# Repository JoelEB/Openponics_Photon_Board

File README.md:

# Openponics_Photon_Board
A water testing platform based off the Particle Photon and the probes and stamps from Atlas Scientific.

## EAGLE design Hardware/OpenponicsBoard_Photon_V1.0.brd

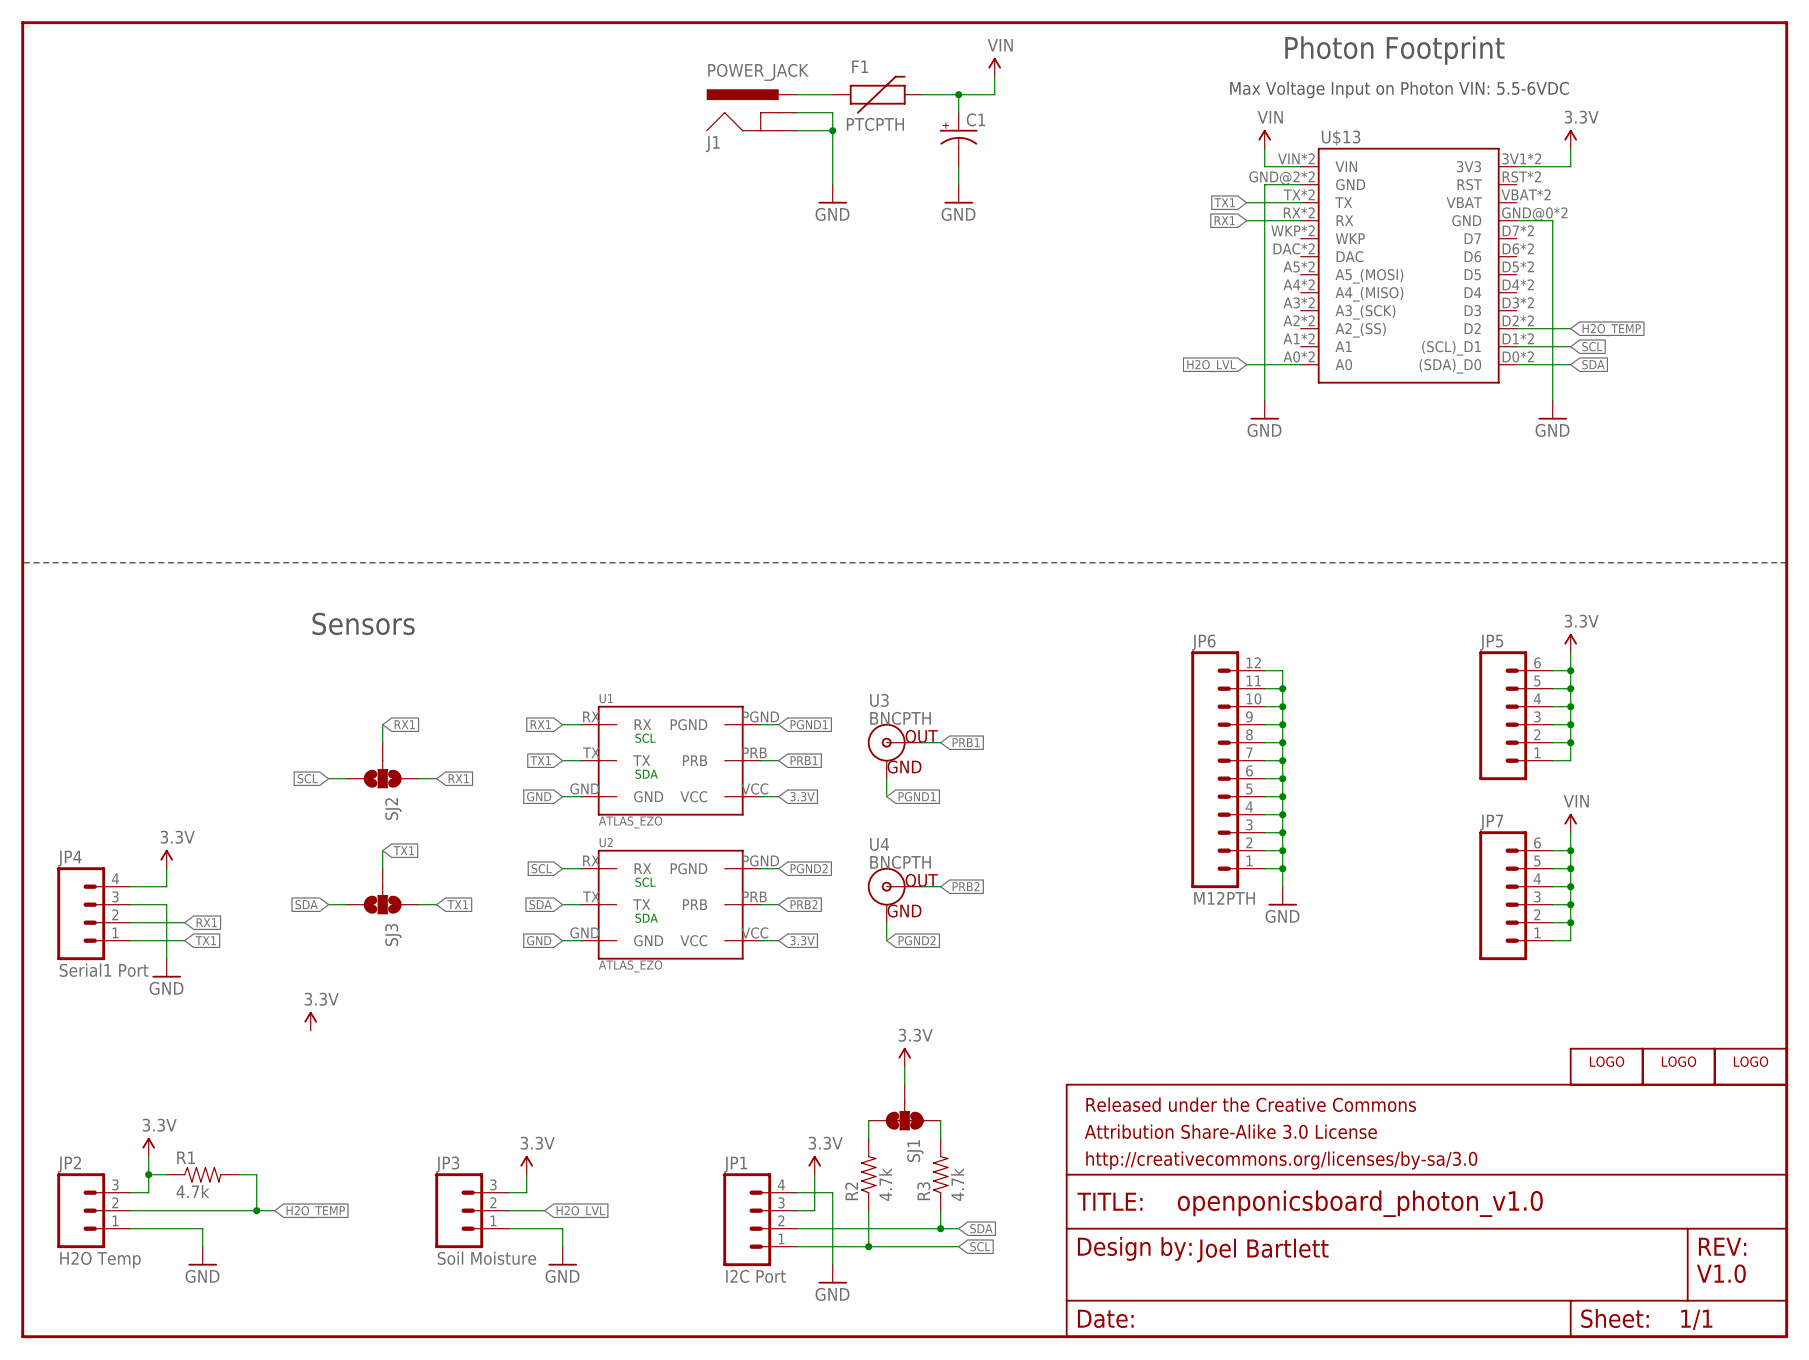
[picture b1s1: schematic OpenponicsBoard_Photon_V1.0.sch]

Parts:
C1: CAP_POLPTH1; CPOL-RADIAL-100UF-25V
F1: PTCPTH; PTC
FRAME1: FRAME-LETTER; CREATIVE_COMMONS
J1: POWER_JACK; POWER_JACK_PTH
JP1: I2C Port; 1X04
JP2: H2O Temp; 1X03
JP3: Soil Moisture; 1X03
JP4: Serial1 Port; 1X04
JP5, JP7: M06SIP; 1X06
JP6: M12PTH; 1X12
R1, R2, R3: 4.7k; AXIAL-0.4
SJ1: JUMPER-PAD-3-NC_BY_TRACE; PAD-JUMPER-3-3OF3_NC_BY_TRACE_YES_SILK_FULL_BOX
SJ2, SJ3: SOLDERJUMPER_2WAYS; SJ_3
U1, U2: ATLAS_EZO
U3, U4: BNCPTH; BNC
U$5: OPENPONICS_LOGO_SYMBOL
U$6: OPENPONICS_LOGO_SMALL
U$9: OPENPONICS_LOGO_SYMBOL_MED
U$13: PHOTON_FOOTPRINT_X2

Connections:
3.3V: JP1.3, JP2.3, JP3.3, JP4.4, JP5.1, JP5.2, JP5.3, JP5.4, JP5.5, JP5.6, R1.P$1 (1), SJ1.2, U1.VCC, U2.VCC, U$13.3V1 (3V3), U$13.3V3
GND: C1.2 (-), J1.GND, J1.GNDBREAK, JP1.4, JP2.1, JP3.1, JP4.3, JP6.1, JP6.2, JP6.3, JP6.4, JP6.5, JP6.6, JP6.7, JP6.8, JP6.9, JP6.10, JP6.11, JP6.12, U1.GND, U2.GND, U$13.GND@0 (GND), U$13.GND@1 (GND), U$13.GND@2 (GND), U$13.GND@2_1 (GND)
H2O_LVL: JP3.2, U$13.A0, U$13.A0_1 (A0)
H2O_TEMP: JP2.2, R1.P$2 (2), U$13.D2, U$13.D2_1 (D2)
unnamed: R2.P$2 (2), SJ1.3
unnamed: R3.P$2 (2), SJ1.1
PGND1: U1.PGND, U3.GND
PGND2: U2.PGND, U4.GND
PRB1: U1.PRB, U3.S (OUT)
PRB2: U2.PRB, U4.S (OUT)
RAW: F1.P$1 (1), J1.PWR
RX1: JP4.2, SJ2.1, SJ2.2, U1.RX, U$13.RX, U$13.RX1 (RX)
SCL: JP1.1, R2.P$1 (1), SJ2.3, U2.RX, U$13.D1 ((SCL)_D1), U$13.D1_1 ((SCL)_D1)
SDA: JP1.2, R3.P$1 (1), SJ3.3, U2.TX, U$13.D0 ((SDA)_D0), U$13.D0_1 ((SDA)_D0)
TX1: JP4.1, SJ3.1, SJ3.2, U1.TX, U$13.TX, U$13.TX1 (TX)
VIN: C1.1 (+), F1.P$2 (2), JP7.1, JP7.2, JP7.3, JP7.4, JP7.5, JP7.6, U$13.VIN, U$13.VIN1 (VIN)

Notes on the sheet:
Sensors
Photon Footprint
Joel Bartlett
V1.0
Max Voltage Input on Photon VIN: 5.5-6VDC
SDA
SCL

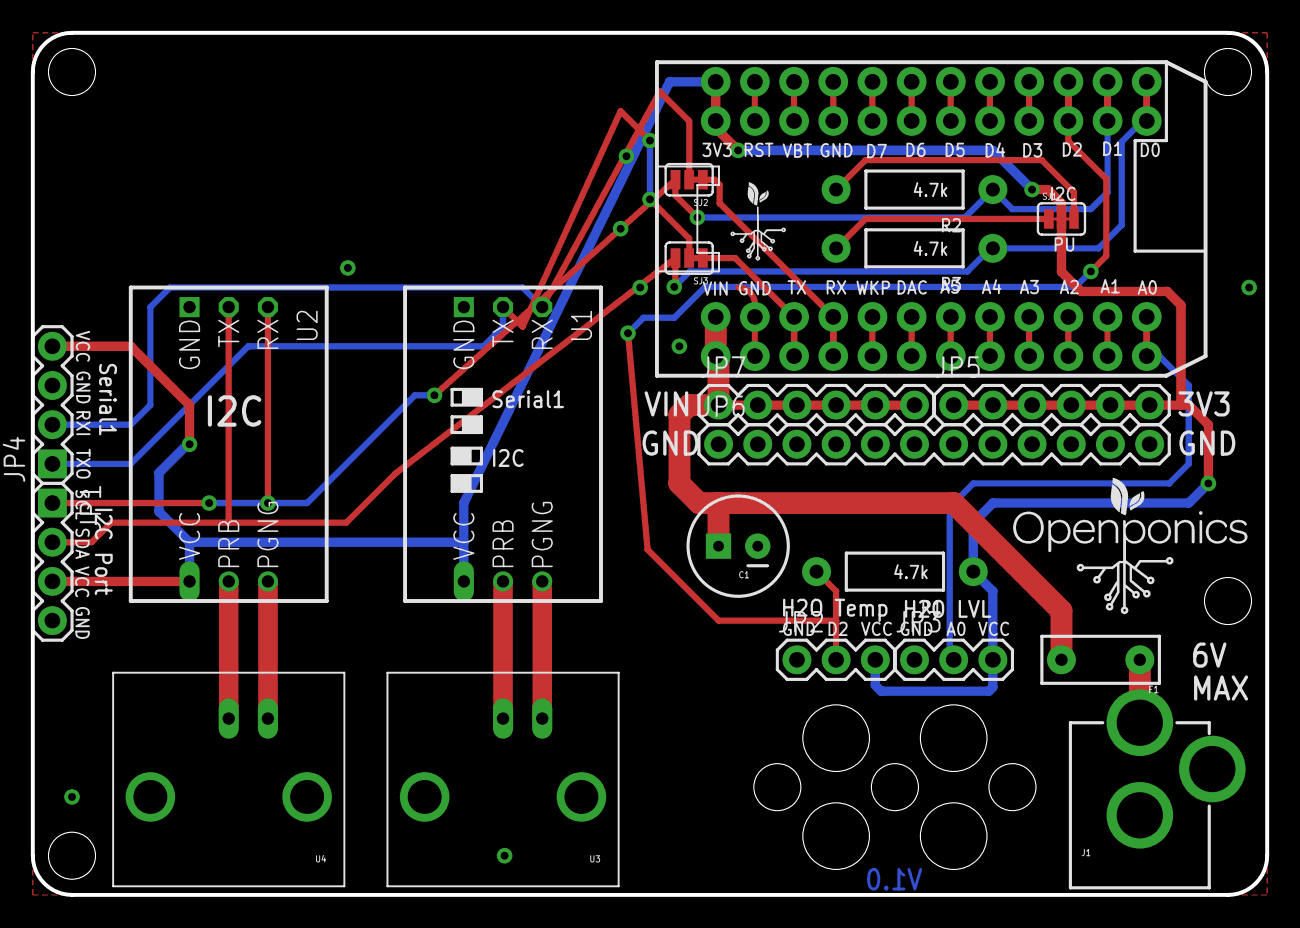
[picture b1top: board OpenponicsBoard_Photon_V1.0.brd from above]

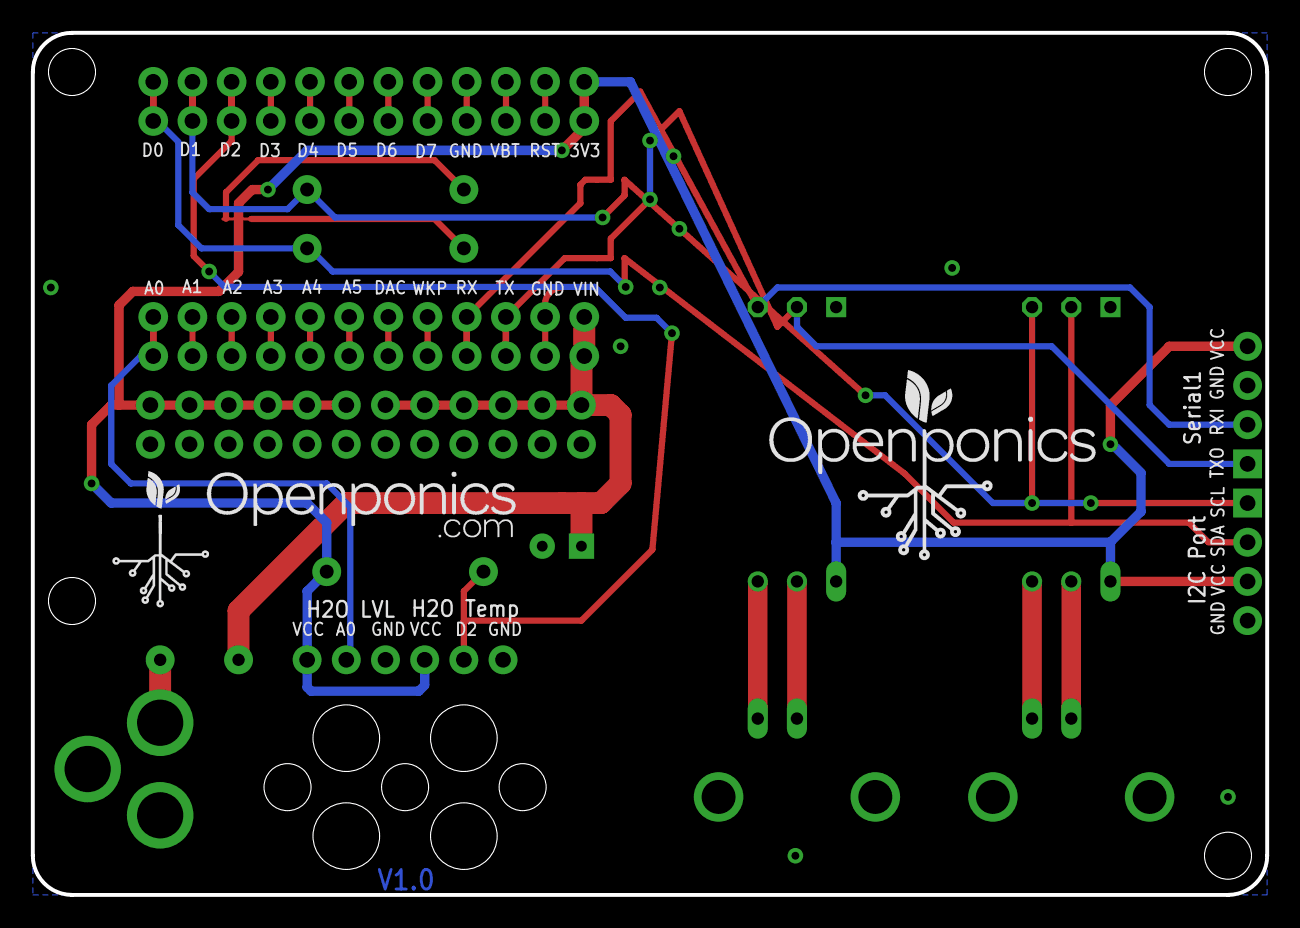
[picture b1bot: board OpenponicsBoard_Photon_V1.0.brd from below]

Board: 2 copper layers, 80.0 x 55.9 mm, 34 parts (3 on the bottom side), 16 nets.

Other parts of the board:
U$1, U$2, U$3, U$4, U$8, U$10, U$11: STAND-OFF-TIGHT
U$7: OPENPONICS_LOGO_MED
U$12: OPENPONICS_LOGO_.COM

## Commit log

2016-02-18 Initial Hardware Commit
2016-02-18 marshall review

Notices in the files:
parts and their libraries:
SparkFun-Aesthetics: Licensing: Creative Commons ShareAlike 4.0 International - https://creativecommons.org/licenses/by-sa/4.0
SparkFun-Aesthetics: Released under the Creative Commons Attribution Share-Alike 3.0 License
SparkFun-Aesthetics: http://creativecommons.org/licenses/by-sa/3.0
